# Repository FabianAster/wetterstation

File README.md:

# Solar Powered Temperatur Sensor with Super Capacitor

This is a small fun project: a temperature sensor running only on solar energy, without a battery.
It contains code for the ESP8266 to connect to an MQTT server, publish its temperature, and then go into deep sleep for 10 seconds.
The Python script captures the readings and stores them in a database.
For charging, it uses a BQ25505 MPPT charger.

## Sensirion SEN69C air-quality sensor

The same collector service also ingests the SEN69C air-quality sensor from
[`../sensirion_test`](../sensirion_test):

```
SEN69C ──MQTT──> Sensirion/measurements/sen69c ──> collect.py ──> sen69c_measurements ──> Grafana
```

- `collectionScript/collect.py` subscribes to both
  `Wetterstation/measurements/#` and `Sensirion/measurements/#`.
- The topic prefix is configured with `MQTT_TOPIC_SEN69C` in
  `collectionScript/.env`.
- `database/migrations/V4__create_sen69c_measurements.sql` creates the
  `sen69c_measurements` table. The collector also applies it idempotently on
  startup, so an existing service picks it up after a restart.
- The Grafana dashboard is provisioned from
  `../stock/grafana/dashboards/sen69c.json`.

Restart the existing collector service after updating:

```bash
sudo systemctl restart collect
```

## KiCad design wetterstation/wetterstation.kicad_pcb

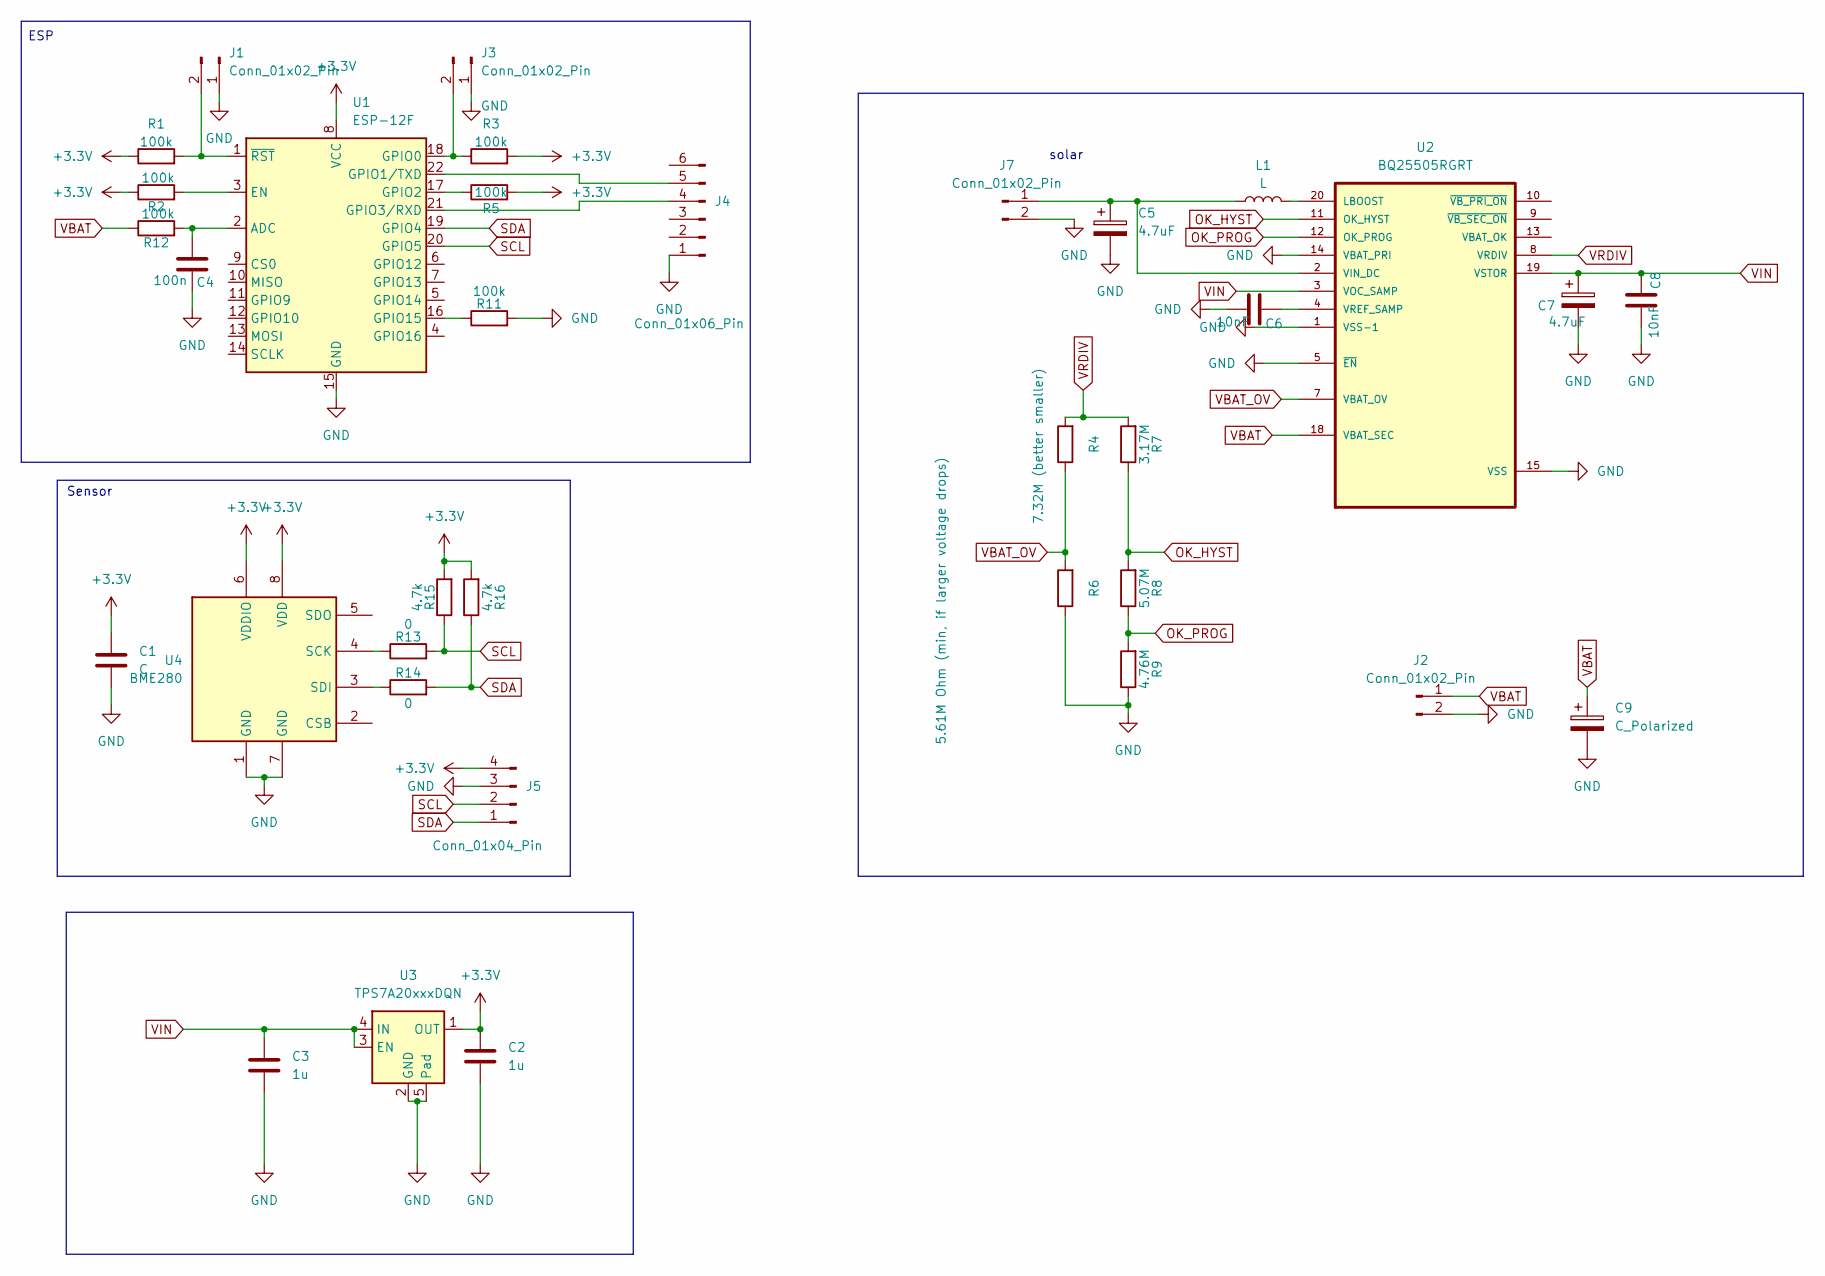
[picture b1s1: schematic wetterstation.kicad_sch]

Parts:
C1: C; C_0603_1608Metric
C2, C3: 1u; C_0603_1608Metric
C4: 100n; C_0603_1608Metric
C5, C7: 4.7uF; CP_Radial_D5.0mm_P2.00mm
C6, C8: 10nF; C_0603_1608Metric
C9: C_Polarized; CP_Radial_D16.0mm_P7.50mm
J1, J2, J3: Conn_01x02_Pin; JST_EH_B2B-EH-A_1x02_P2.50mm_Vertical
J4: Conn_01x06_Pin; JST_EH_B6B-EH-A_1x06_P2.50mm_Vertical
J5: Conn_01x04_Pin; JST_EH_B4B-EH-A_1x04_P2.50mm_Vertical
J7: Conn_01x02_Pin; JST_NV_B02P-NV_1x02_P5.00mm_Vertical
L1: L; L_Abracon_ASPI-0425
R1, R2, R3, R5, R11, R12: 100k; R_1206_3216Metric
R4: 7.32M (better smaller); R_1206_3216Metric
R6: 5.61M Ohm (min, if larger voltage drops); R_1206_3216Metric
R7: 3.17M; R_1206_3216Metric
R8: 5.07M; R_1206_3216Metric
R9: 4.76M; R_1206_3216Metric
R13, R14: 0; R_1206_3216Metric
R15, R16: 4.7k; R_1206_3216Metric
U1: ESP-12F; ESP-12E
U2: BQ25505RGRT; QFN50P350X350X100-21N
U3: TPS7A20xxxDQN; Texas_X2SON-4_1x1mm_P0.65mm
U4: BME280; Bosch_LGA-8_2.5x2.5mm_P0.65mm_ClockwisePinNumbering

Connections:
+3.3V: C1.1, C2.1, J5.4, R1.1, R2.1, R3.2, R5.2, R15.2, R16.2, U1.8 (VCC), U3.1 (OUT), U4.6 (VDDIO), U4.8 (VDD)
GND: C1.2, C2.2, C3.2, C4.2, C5.2, C6.1, C7.2, C8.1, C9.2, J1.1, J2.2, J3.1, J4.1, J5.3, J7.2, R6.1, R9.1, R11.2, U1.15 (GND), U2.1 (VSS-1), U2.5 (~EN), U2.14 (VBAT_PRI), U2.15 (VSS), U3.2 (GND), U3.5 (Pad), U4.1 (GND), U4.7 (GND)
unnamed: J1.2, R1.2, U1.1 (~RST)
unnamed: J3.2, R3.1, U1.18 (GPIO0)
unnamed: J4.4, U1.21 (GPIO3/RXD)
unnamed: J4.5, U1.22 (GPIO1/TXD)
unnamed: C5.1, J7.1, L1.1, U2.2 (VIN_DC)
unnamed: C4.1, R12.2, U1.2 (ADC)
unnamed: R2.2, U1.3 (EN)
unnamed: R5.1, U1.17 (GPIO2)
unnamed: R11.1, U1.16 (GPIO15)
unnamed: L1.2, U2.20 (LBOOST)
unnamed: C6.2, U2.4 (VREF_SAMP)
unnamed: R13.1, U4.4 (SCK)
unnamed: R14.1, U4.3 (SDI)
OK_HYST: R7.1, R8.2, U2.11 (OK_HYST)
OK_PROG: R8.1, R9.2, U2.12 (OK_PROG)
SCL: J5.2, R13.2, R15.1, U1.20 (GPIO5)
SDA: J5.1, R14.2, R16.1, U1.19 (GPIO4)
VBAT: C9.1, J2.1, R12.1, U2.18 (VBAT_SEC)
VBAT_OV: R4.1, R6.2, U2.7 (VBAT_OV)
VIN: C3.1, C7.1, C8.2, U2.3 (VOC_SAMP), U2.19 (VSTOR), U3.3 (EN), U3.4 (IN)
VRDIV: R4.2, R7.2, U2.8 (VRDIV)

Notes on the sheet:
ESP
Sensor
solar

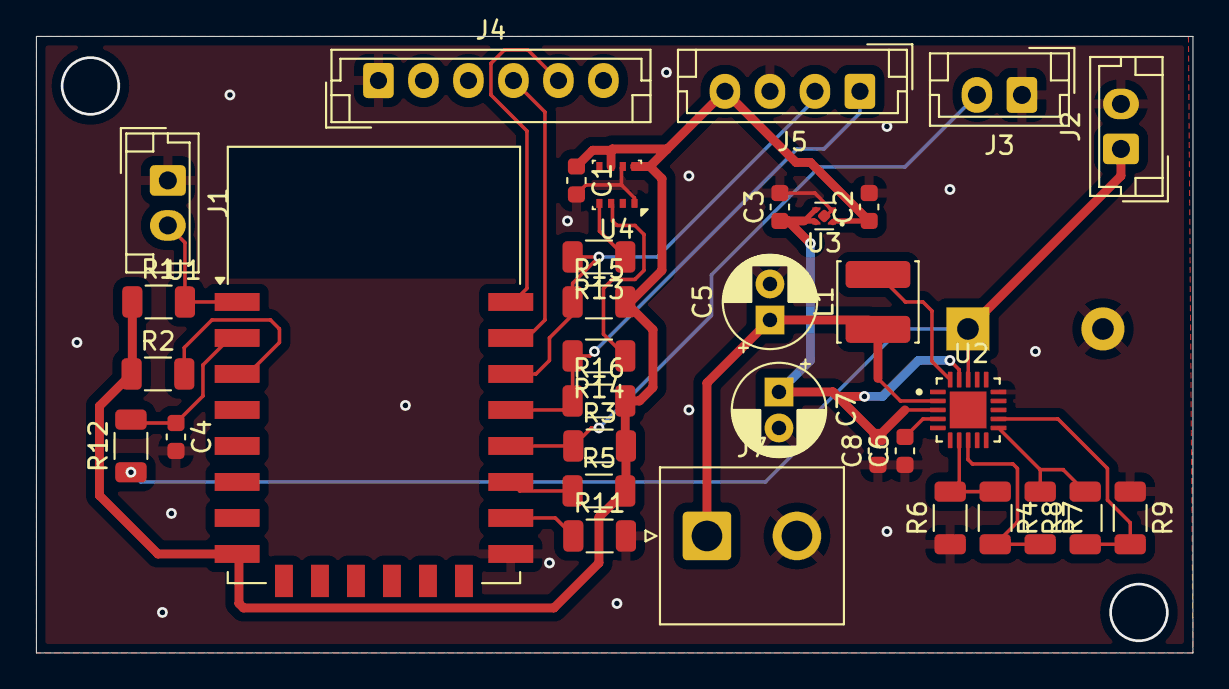
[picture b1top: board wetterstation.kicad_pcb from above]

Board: 2 copper layers, 64.2 x 34.2 mm, 35 parts (1 on the bottom side), 23 nets.

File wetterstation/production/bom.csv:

Designator,Footprint,Quantity,Value,LCSC Part #
C1,0603,1,C,
"C2, C3",0603,2,1u,
C4,0603,1,100n,
"C5, C7",CP_Radial_D5.0mm_P2.00mm,2,4.7uF,
"C6, C8",0603,2,10nF,
C9,CP_Radial_D16.0mm_P7.50mm,1,C_Polarized,
"J1, J2, J3",JST_EH_B2B-EH-A_1x02_P2.50mm_Vertical,3,Conn_01x02_Pin,
J4,JST_EH_B6B-EH-A_1x06_P2.50mm_Vertical,1,Conn_01x06_Pin,
J5,JST_EH_B4B-EH-A_1x04_P2.50mm_Vertical,1,Conn_01x04_Pin,
J7,JST_NV_B02P-NV_1x02_P5.00mm_Vertical,1,Conn_01x02_Pin,
L1,L_Abracon_ASPI-0425,1,L,
"R1, R11, R12, R2, R3, R5",1206,6,100k,
"R13, R14",1206,2,0,
"R15, R16",1206,2,4.7k,
R4,1206,1,7.32M (better smaller),
R6,1206,1,"5.61M Ohm (min, if larger voltage drops)",
R7,1206,1,3.17M,
R8,1206,1,5.07M,
R9,1206,1,4.76M,
U1,ESP-12E,1,ESP-12F,
U2,QFN50P350X350X100-21N,1,BQ25505RGRT,
U3,Texas_X2SON-4_1x1mm_P0.65mm,1,TPS7A20xxxDQN,
U4,Bosch_LGA-8_2.5x2.5mm_P0.65mm_ClockwisePinNumbering,1,BME280,

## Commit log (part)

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2025-09-27 init commit
2025-09-27 added script
2025-10-02 working with sensor
2025-10-02 updated collectionScript
2025-10-02 updated to store full topic
2025-10-05 added small readme
2025-11-20 added air quality logic for esp
2025-11-20 extended db and collection scrip
2025-11-20 fixed migration issue
2026-04-28 added garage zuig
